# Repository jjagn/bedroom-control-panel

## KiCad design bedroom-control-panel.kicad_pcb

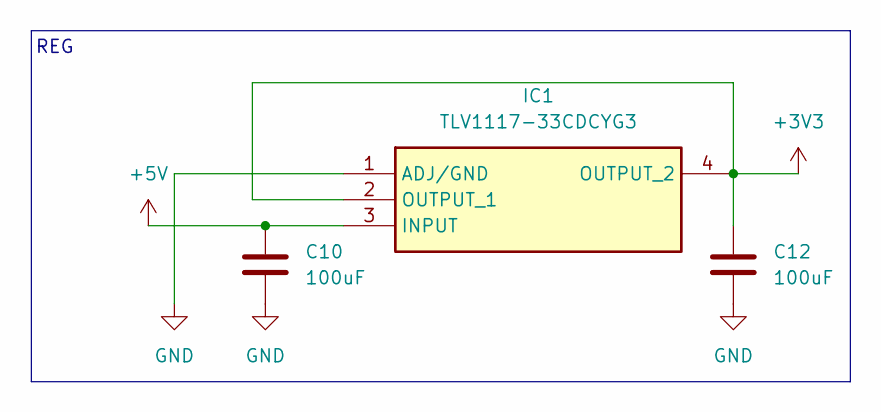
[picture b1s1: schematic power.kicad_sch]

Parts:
C10, C12: 100uF; C_1206_3216Metric
IC1: TLV1117-33CDCYG3; SOT230P700X180-4N; Manufacturer_Part_Number TLV1117-33CDCYG3; Mouser Part Number 595-TLV1117-33CDCYG3

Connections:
+3V3: C12.1, IC1.2 (OUTPUT_1), IC1.4 (OUTPUT_2); also elsewhere on the board
+5V: C10.1, IC1.3 (INPUT); also elsewhere on the board
GND: C10.2, C12.2, IC1.1 (ADJ/GND); also elsewhere on the board

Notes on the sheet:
REG

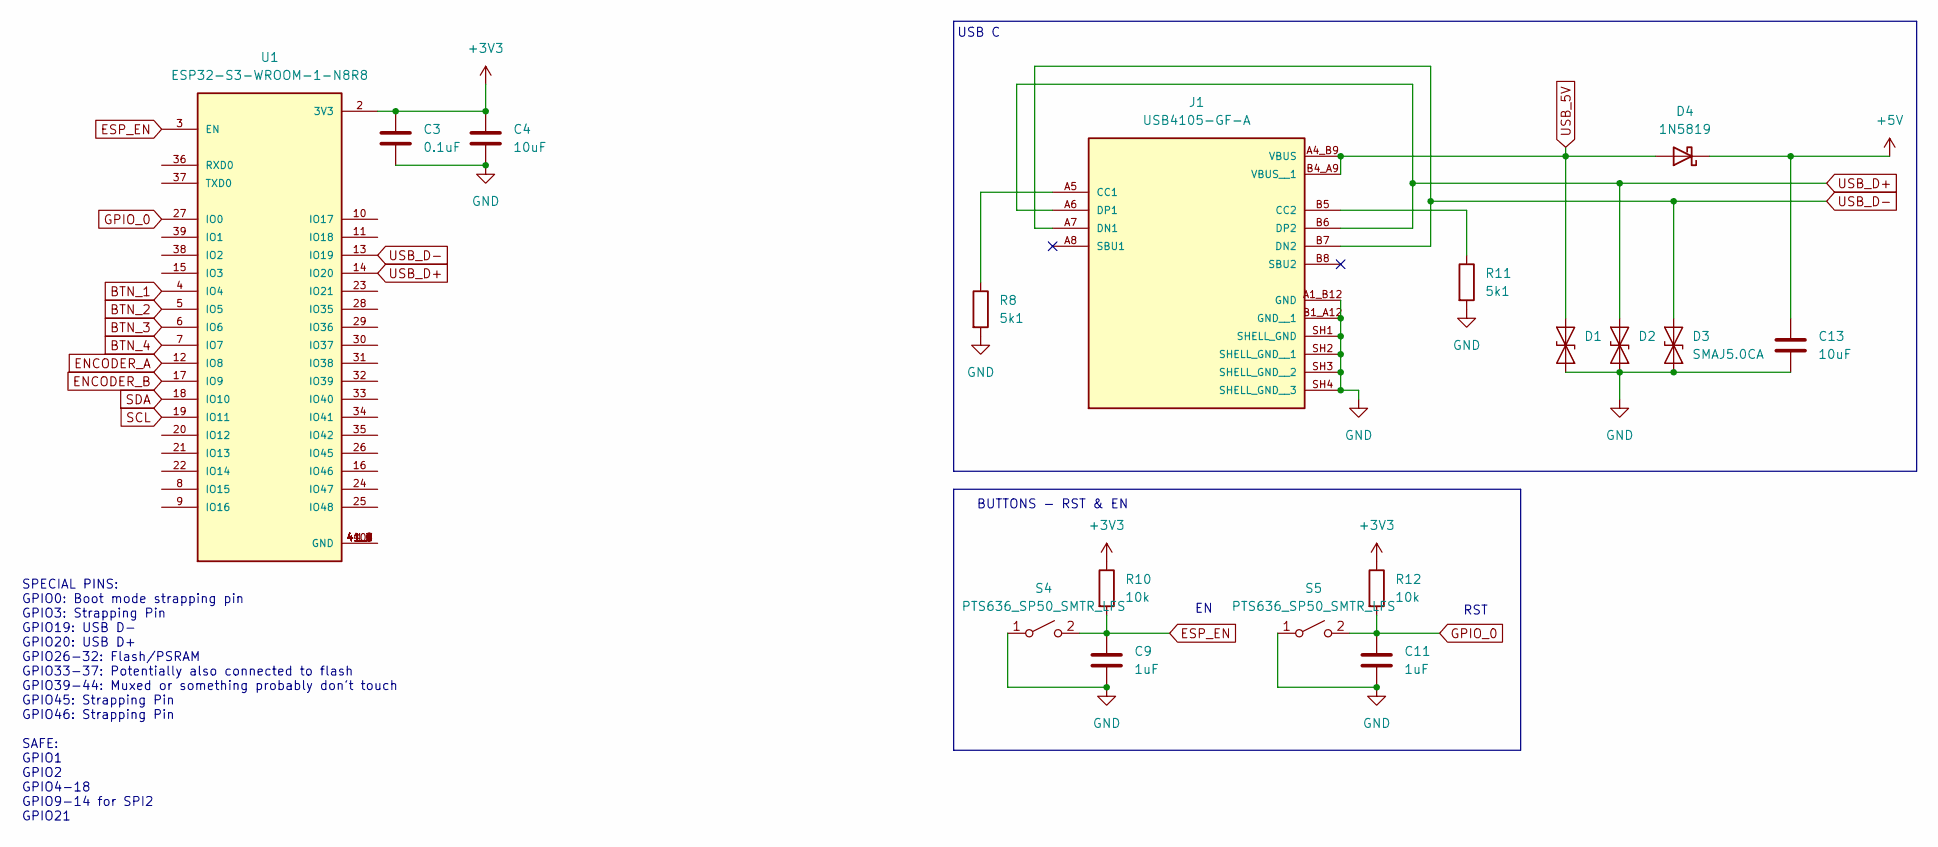
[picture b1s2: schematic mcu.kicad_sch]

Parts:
C3: 0.1uF; C_1206_3216Metric
C4, C13: 10uF; C_1206_3216Metric
C9, C11: 1uF; C_1206_3216Metric
D1, D2, D3: SMAJ5.0CA; D_SMA
D4: 1N5819; D_DO-41_SOD81_P10.16mm_Horizontal
J1: USB4105-GF-A; USB4105-GF-A_GCT_USB4105-GF-A; PARTREV B4
R8, R11: 5k1; R_1206_3216Metric_Pad1.30x1.75mm_HandSolder
R10, R12: 10k; R_1206_3216Metric_Pad1.30x1.75mm_HandSolder
S4, S5: PTS636_SP50_SMTR_LFS; PTS636SP50SMTRLFS; Mouser Part Number 611-PTS636SP50SMTRLF
U1: ESP32-S3-WROOM-1-N8R8; ESP32-S3-WROOM-1-N8R8_XCVR_ESP32S3WROOM1N8R8

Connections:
+3V3: C3.1, C4.1, R10.1, R12.1, U1.2 (3V3); also elsewhere on the board
+5V: C13.1, D4.1 (K); also elsewhere on the board
BTN_1: U1.4 (IO4); also elsewhere on the board
BTN_2: U1.5 (IO5); also elsewhere on the board
BTN_3: U1.6 (IO6); also elsewhere on the board
BTN_4: U1.7 (IO7); also elsewhere on the board
ENCODER_A: U1.12 (IO8); also elsewhere on the board
ENCODER_B: U1.17 (IO9); also elsewhere on the board
ESP_EN: C9.1, R10.2, S4.2 (B), U1.3 (EN)
GND: C3.2, C4.2, C9.2, C11.2, C13.2, D1.1 (A1), D2.1 (A1), D3.1 (A1), J1.A1_B12 (GND), J1.B1_A12 (GND__1), J1.SH1 (SHELL_GND), J1.SH2 (SHELL_GND__1), J1.SH3 (SHELL_GND__2), J1.SH4 (SHELL_GND__3), R8.2, R11.2, S4.1 (A), S5.1 (A); also elsewhere on the board
GPIO_0: C11.1, R12.2, S5.2 (B), U1.27 (IO0)
unnamed: J1.A5 (CC1), R8.1
unnamed: J1.B5 (CC2), R11.1
unnamed: U1.1 (GND), U1.40 (GND), U1.41_1 (GND), U1.41_2 (GND), U1.41_3 (GND), U1.41_4 (GND), U1.41_5 (GND), U1.41_6 (GND), U1.41_7 (GND), U1.41_8 (GND), U1.41_9 (GND)
SCL: U1.19 (IO11); also elsewhere on the board
SDA: U1.18 (IO10); also elsewhere on the board
USB_5V: D1.2 (A2), D4.2 (A), J1.A4_B9 (VBUS), J1.B4_A9 (VBUS__1)
USB_D+: D2.2 (A2), J1.A6 (DP1), J1.B6 (DP2), U1.14 (IO20)
USB_D-: D3.2 (A2), J1.A7 (DN1), J1.B7 (DN2), U1.13 (IO19)

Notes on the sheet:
USB C
RST
SPECIAL PINS: GPIO0: Boot mode strapping pin GPIO3: Strapping Pin GPIO19: USB D- GPIO20: USB D+ GPIO26-32: Flash/PSRAM GPIO33-37: Potentially also connected to flash GPIO39-44: Muxed or something probably don't touch GPIO45: Strapping Pin GPIO46: Strapping Pin SAFE: GPIO1 GPIO2 GPIO4-18 GPIO9-14 fo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
BUTTONS - RST & EN

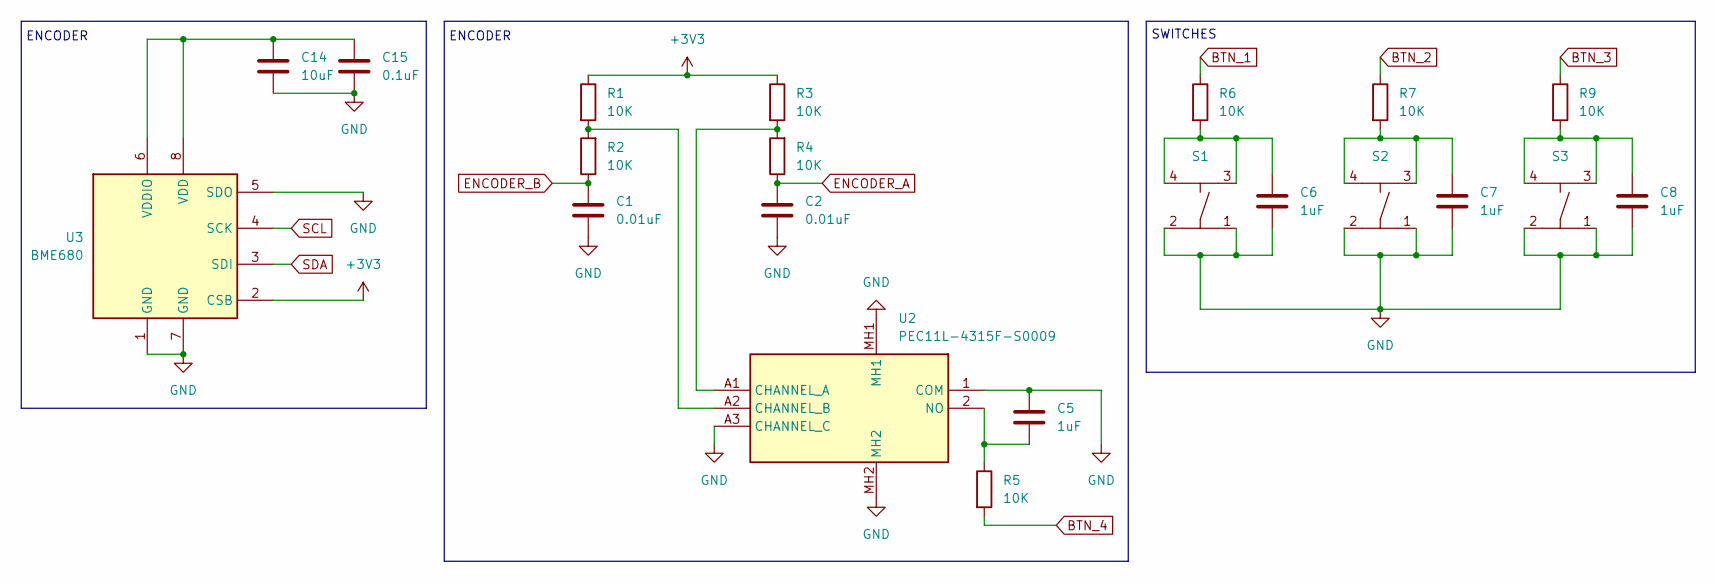
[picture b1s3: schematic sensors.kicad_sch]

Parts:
C1, C2: 0.01uF; C_1206_3216Metric
C5, C6, C7, C8: 1uF; C_1206_3216Metric
C14: 10uF; C_1206_3216Metric
C15: 0.1uF; C_1206_3216Metric
R1, R2, R3, R4, R5, R6, R7, R9: 10K; R_1206_3216Metric_Pad1.30x1.75mm_HandSolder
S1, S2, S3: B3FS-1050
U2: PEC11L-4315F-S0009; PEC11L4315FS0009; Manufacturer_Part_Number PEC11L-4315F-S0009
U3: BME680; Bosch_LGA-8_3x3mm_P0.8mm_ClockwisePinNumbering

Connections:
+3V3: R1.1, R3.1, U3.2 (CSB); also elsewhere on the board
BTN_1: R6.1; also elsewhere on the board
BTN_2: R7.1; also elsewhere on the board
BTN_3: R9.1; also elsewhere on the board
BTN_4: R5.2; also elsewhere on the board
ENCODER_A: C2.1, R4.1; also elsewhere on the board
ENCODER_B: C1.1, R2.1; also elsewhere on the board
GND: C1.2, C2.2, C5.1, C6.2, C7.2, C8.2, C14.2, C15.2, S1.1, S1.2, S2.1, S2.2, S3.1, S3.2, U2.1 (COM), U2.A3 (CHANNEL_C), U2.MH1, U2.MH2, U3.1 (GND), U3.5 (SDO), U3.7 (GND); also elsewhere on the board
unnamed: C6.1, R6.2, S1.3, S1.4
unnamed: C7.1, R7.2, S2.3, S2.4
unnamed: C8.1, R9.2, S3.3, S3.4
unnamed: R3.2, R4.2, U2.A1 (CHANNEL_A)
unnamed: R1.2, R2.2, U2.A2 (CHANNEL_B)
unnamed: C5.2, R5.1, U2.2 (NO)
unnamed: C14.1, C15.1, U3.6 (VDDIO), U3.8 (VDD)
SCL: U3.4 (SCK); also elsewhere on the board
SDA: U3.3 (SDI); also elsewhere on the board

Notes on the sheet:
SWITCHES
ENCODER

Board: 2 copper layers, 41 parts (6 on the bottom side), 26 nets, no tracks yet.

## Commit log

2025-01-24 schematic complete, added bme680
